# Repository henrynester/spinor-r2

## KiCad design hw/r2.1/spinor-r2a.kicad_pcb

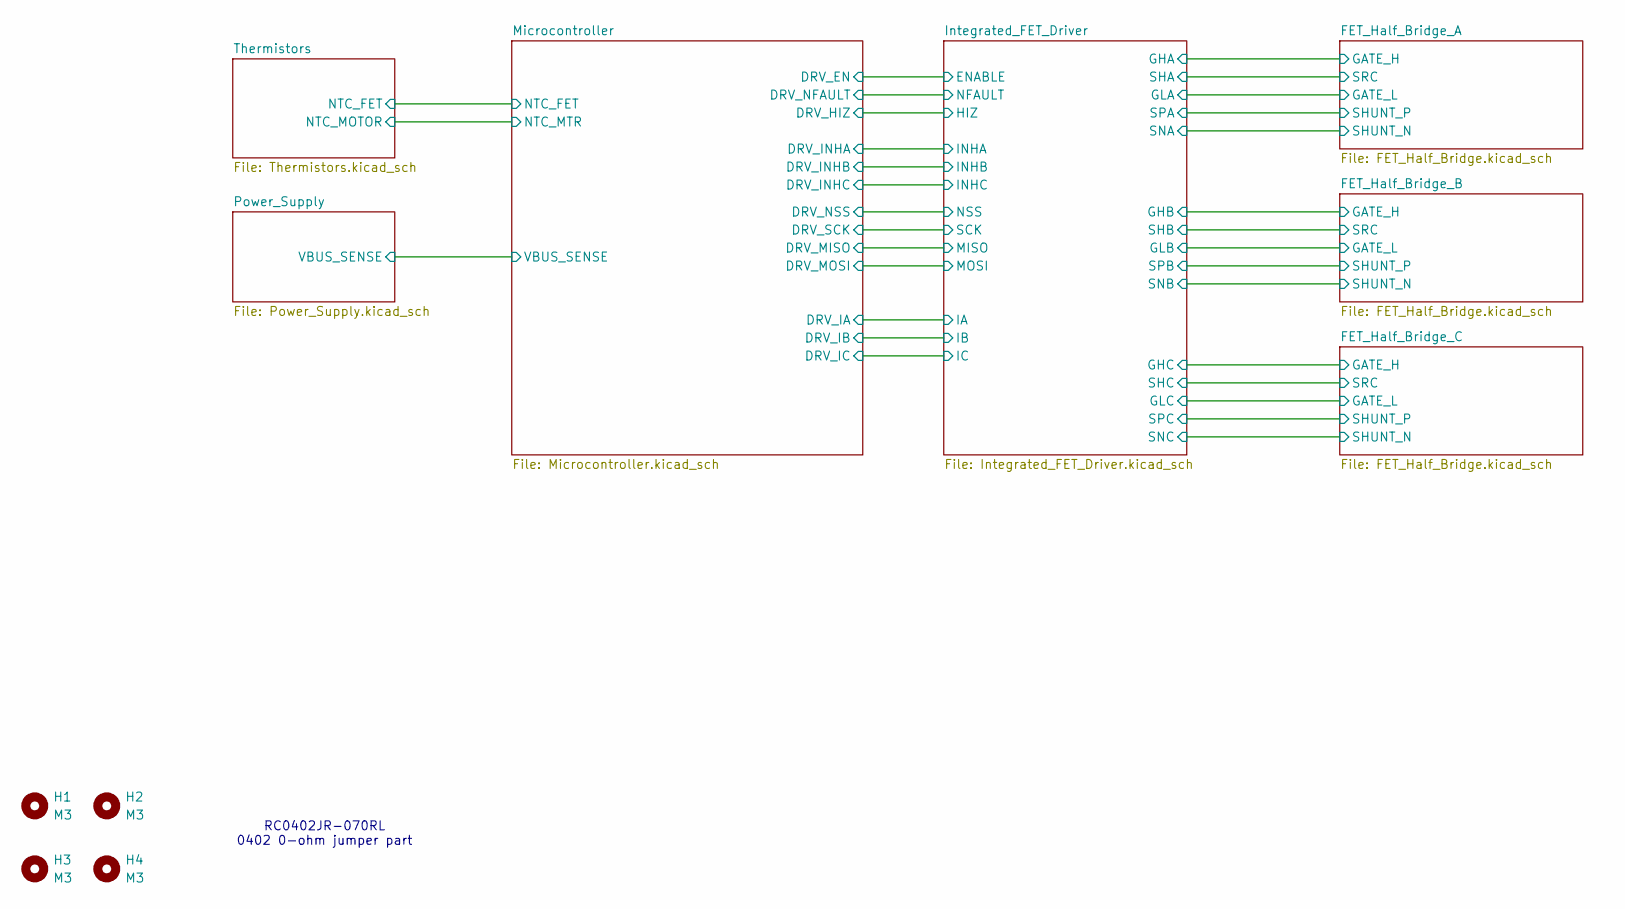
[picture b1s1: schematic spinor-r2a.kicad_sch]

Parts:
H1, H2, H3, H4: M3; MountingHole_3.2mm_M3_Pad_Via

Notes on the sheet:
RC0402JR-070RL 0402 0-ohm jumper part

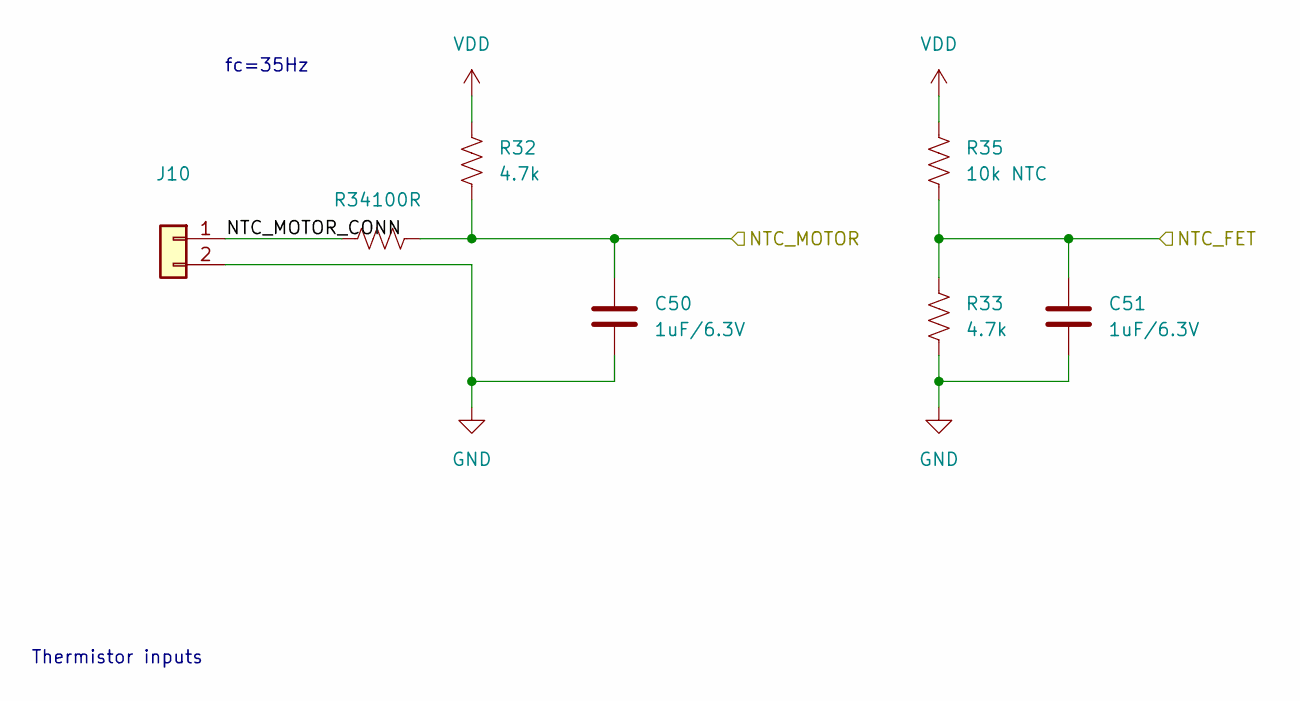
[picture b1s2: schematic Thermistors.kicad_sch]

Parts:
C50, C51: 1uF/6.3V; hn_C_0402; part Murata GRM155R70J105KA12D
J10: PinHeader_1x02_P1.27mm_Vertical
R32, R33: 4.7k; hn_R_0402; part YAGEO RC0402JR-074K7L
R34: 100R; hn_R_0402; part YAGEO RC0402FR-07100RL
R35: 10k NTC; hn_R_0805; part Murata NCP21XV103J03RA

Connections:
/Microcontroller/ADC12_IN1: C50.1, R32.2, R34.2; also elsewhere on the board
/Microcontroller/ADC12_IN2: C51.1, R33.1, R35.2; also elsewhere on the board
/Thermistors/NTC_MOTOR_CONN: J10.1, R34.1
GND: C50.2, C51.2, J10.2, R33.2; also elsewhere on the board

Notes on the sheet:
fc=35Hz
Thermistor inputs

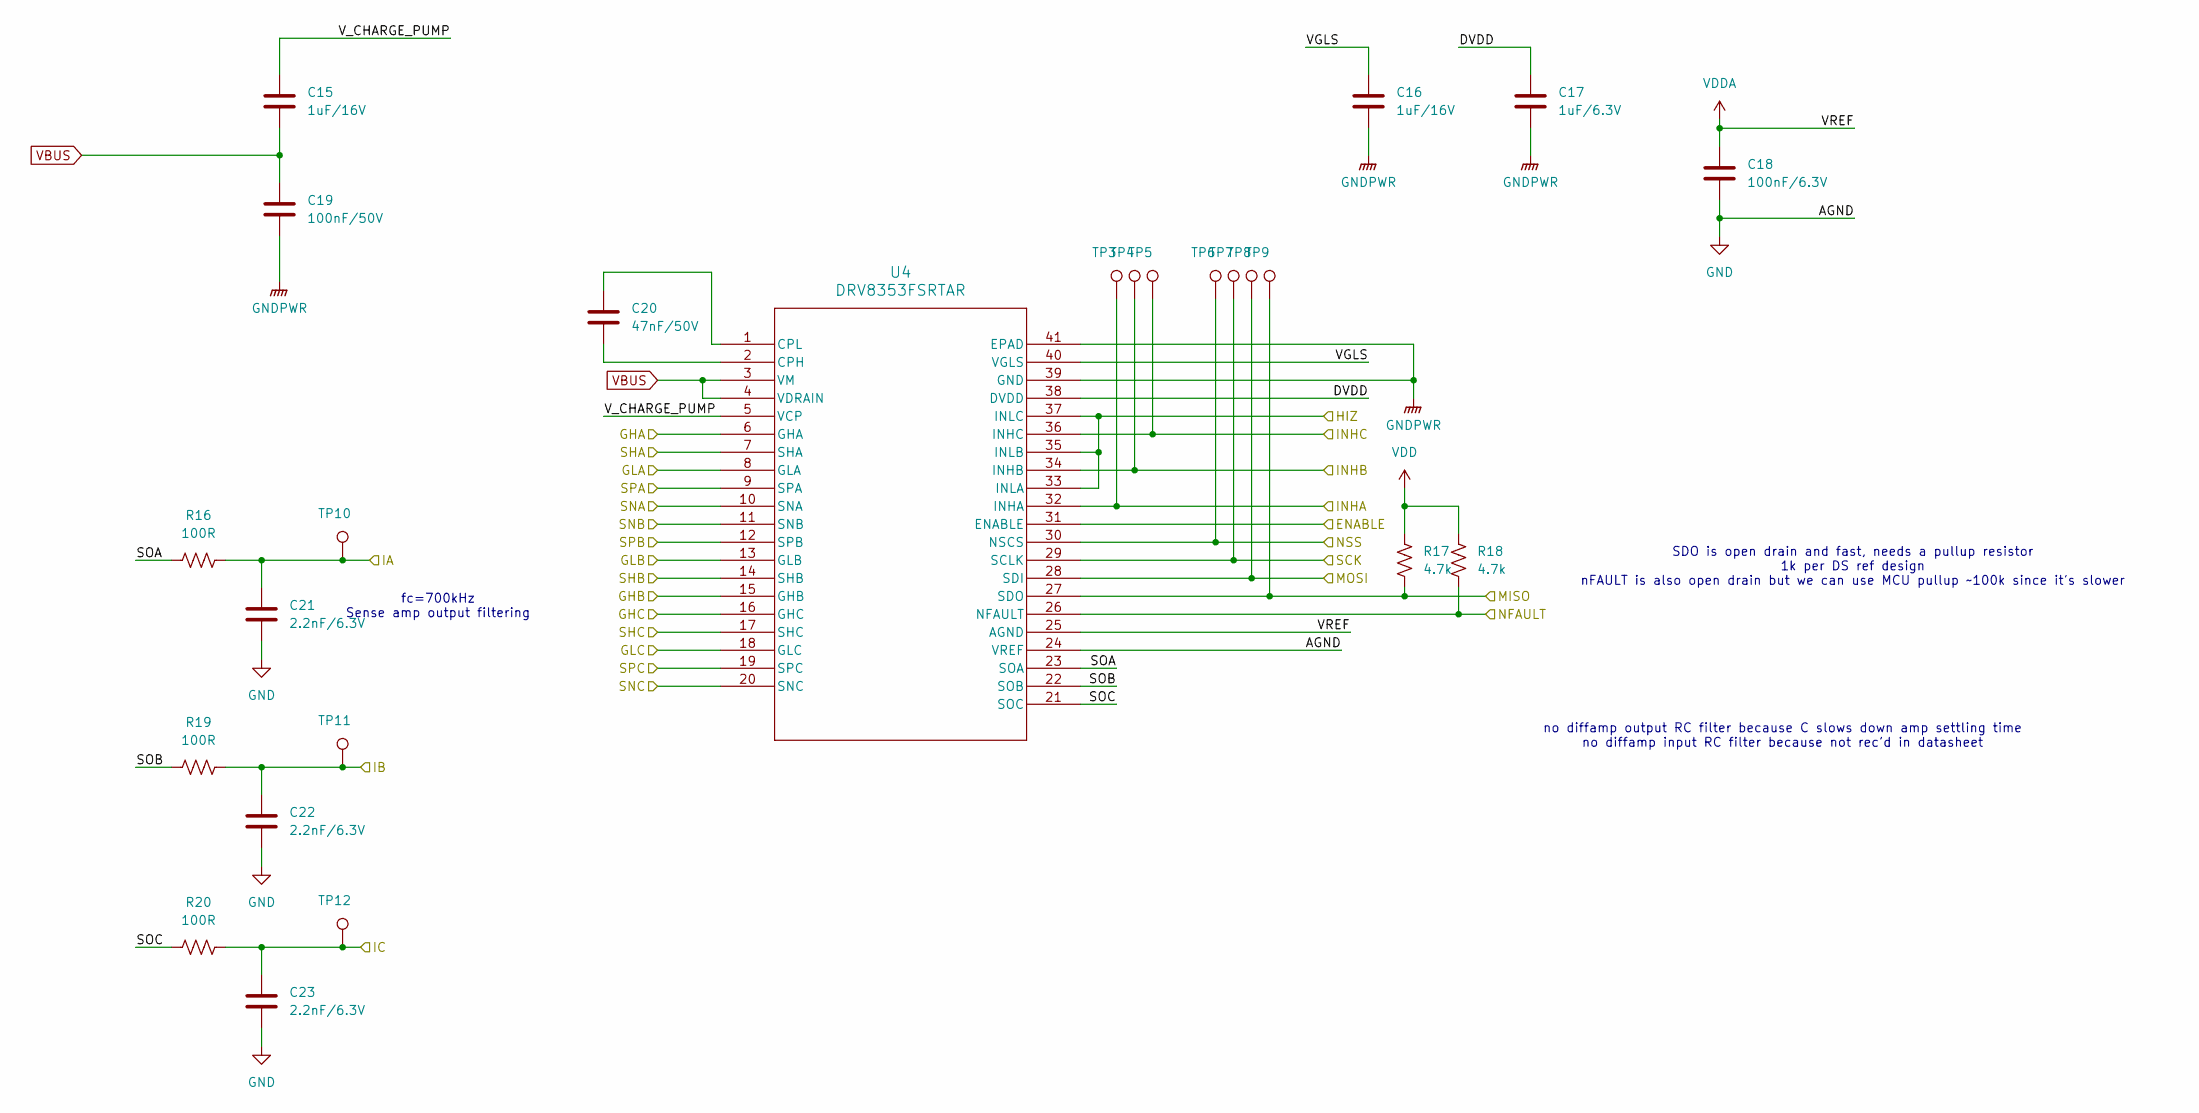
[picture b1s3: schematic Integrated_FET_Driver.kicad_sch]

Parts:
C15, C16: 1uF/16V; hn_C_0603; part Murata GCM188R71C105KA64D
C17: 1uF/6.3V; hn_C_0402; part Murata GRM155R70J105KA12D
C18: 100nF/6.3V; hn_C_0402; part Murata GRM155R70J104KA01D
C19: 100nF/50V; hn_C_0603; part Murata GCJ188R71H104KA12D
C20: 47nF/50V; hn_C_0402; part Murata GRM155R71H473KE14D
C21, C22, C23: 2.2nF/6.3V; hn_C_0402; part Murata GRM155R70J222KA01D
R16, R19, R20: 100R; hn_R_0402; part YAGEO RC0402FR-07100RL
R17, R18: 4.7k; hn_R_0402; part YAGEO RC0402JR-074K7L
TP3, TP4, TP5, TP6, TP7, TP8, TP9, TP10, TP11, TP12: PinHeader_1x01_P1.00mm_Vertical
U4: DRV8353FSRTAR; hn_TexasInstruments_WQFN40; part Texas Instruments DRV8353FSRTAR

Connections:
/FET_Half_Bridge_A/GATE_H: U4.6 (GHA); also elsewhere on the board
/FET_Half_Bridge_A/GATE_L: U4.8 (GLA); also elsewhere on the board
/FET_Half_Bridge_A/PHASE: U4.7 (SHA); also elsewhere on the board
/FET_Half_Bridge_A/SHUNT_P: U4.9 (SPA); also elsewhere on the board
/FET_Half_Bridge_B/GATE_H: U4.15 (GHB); also elsewhere on the board
/FET_Half_Bridge_B/GATE_L: U4.13 (GLB); also elsewhere on the board
/FET_Half_Bridge_B/PHASE: U4.14 (SHB); also elsewhere on the board
/FET_Half_Bridge_B/SHUNT_P: U4.12 (SPB); also elsewhere on the board
/FET_Half_Bridge_C/GATE_H: U4.16 (GHC); also elsewhere on the board
/FET_Half_Bridge_C/GATE_L: U4.18 (GLC); also elsewhere on the board
/FET_Half_Bridge_C/PHASE: U4.17 (SHC); also elsewhere on the board
/FET_Half_Bridge_C/SHUNT_P: U4.19 (SPC); also elsewhere on the board
/Integrated_FET_Driver/DVDD: C17.1, U4.38 (DVDD)
/Integrated_FET_Driver/SOA: R16.1, U4.23 (SOA)
/Integrated_FET_Driver/SOB: R19.1, U4.22 (SOB)
/Integrated_FET_Driver/SOC: R20.1, U4.21 (SOC)
/Integrated_FET_Driver/VGLS: C16.2, U4.40 (VGLS)
/Integrated_FET_Driver/V_CHARGE_PUMP: C15.2, U4.5 (VCP)
/Microcontroller/ADC1_IN12: C21.1, R16.2, TP10.1; also elsewhere on the board
/Microcontroller/ADC2_IN12: C22.1, R19.2, TP11.1; also elsewhere on the board
/Microcontroller/ADC3_IN12: C23.1, R20.2, TP12.1; also elsewhere on the board
/Microcontroller/PA7: U4.31 (ENABLE); also elsewhere on the board
/Microcontroller/PA11: U4.33 (INLA), U4.35 (INLB), U4.37 (INLC); also elsewhere on the board
/Microcontroller/PA12: R18.2, U4.26 (NFAULT); also elsewhere on the board
/Microcontroller/SPI1_MISO: R17.2, TP9.1, U4.27 (SDO); also elsewhere on the board
/Microcontroller/SPI1_MOSI: TP8.1, U4.28 (SDI); also elsewhere on the board
/Microcontroller/SPI1_NSS: TP6.1, U4.30 (NSCS); also elsewhere on the board
/Microcontroller/SPI1_SCK: TP7.1, U4.29 (SCLK); also elsewhere on the board
/Microcontroller/TIM1_CH1: TP3.1, U4.32 (INHA); also elsewhere on the board
/Microcontroller/TIM1_CH2: TP4.1, U4.34 (INHB); also elsewhere on the board
/Microcontroller/TIM1_CH3: TP5.1, U4.36 (INHC); also elsewhere on the board
GND: C16.1, C17.2, C18.2, C19.2, C21.2, C22.2, C23.2, U4.10 (SNA), U4.11 (SNB), U4.20 (SNC), U4.24 (VREF), U4.39 (GND), U4.41 (EPAD); also elsewhere on the board
unnamed: C20.2, U4.2 (CPH)
unnamed: C20.1, U4.1 (CPL)
VBUS: C15.1, C19.1, U4.3 (VM), U4.4 (VDRAIN); also elsewhere on the board

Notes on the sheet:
SDO is open drain and fast, needs a pullup resistor 1k per DS ref design nFAULT is also open drain but we can use MCU pullup ~100k since it's slower
fc=700kHz Sense amp output filtering
no diffamp output RC filter because C slows down amp settling time no diffamp input RC filter because not rec'd in datasheet

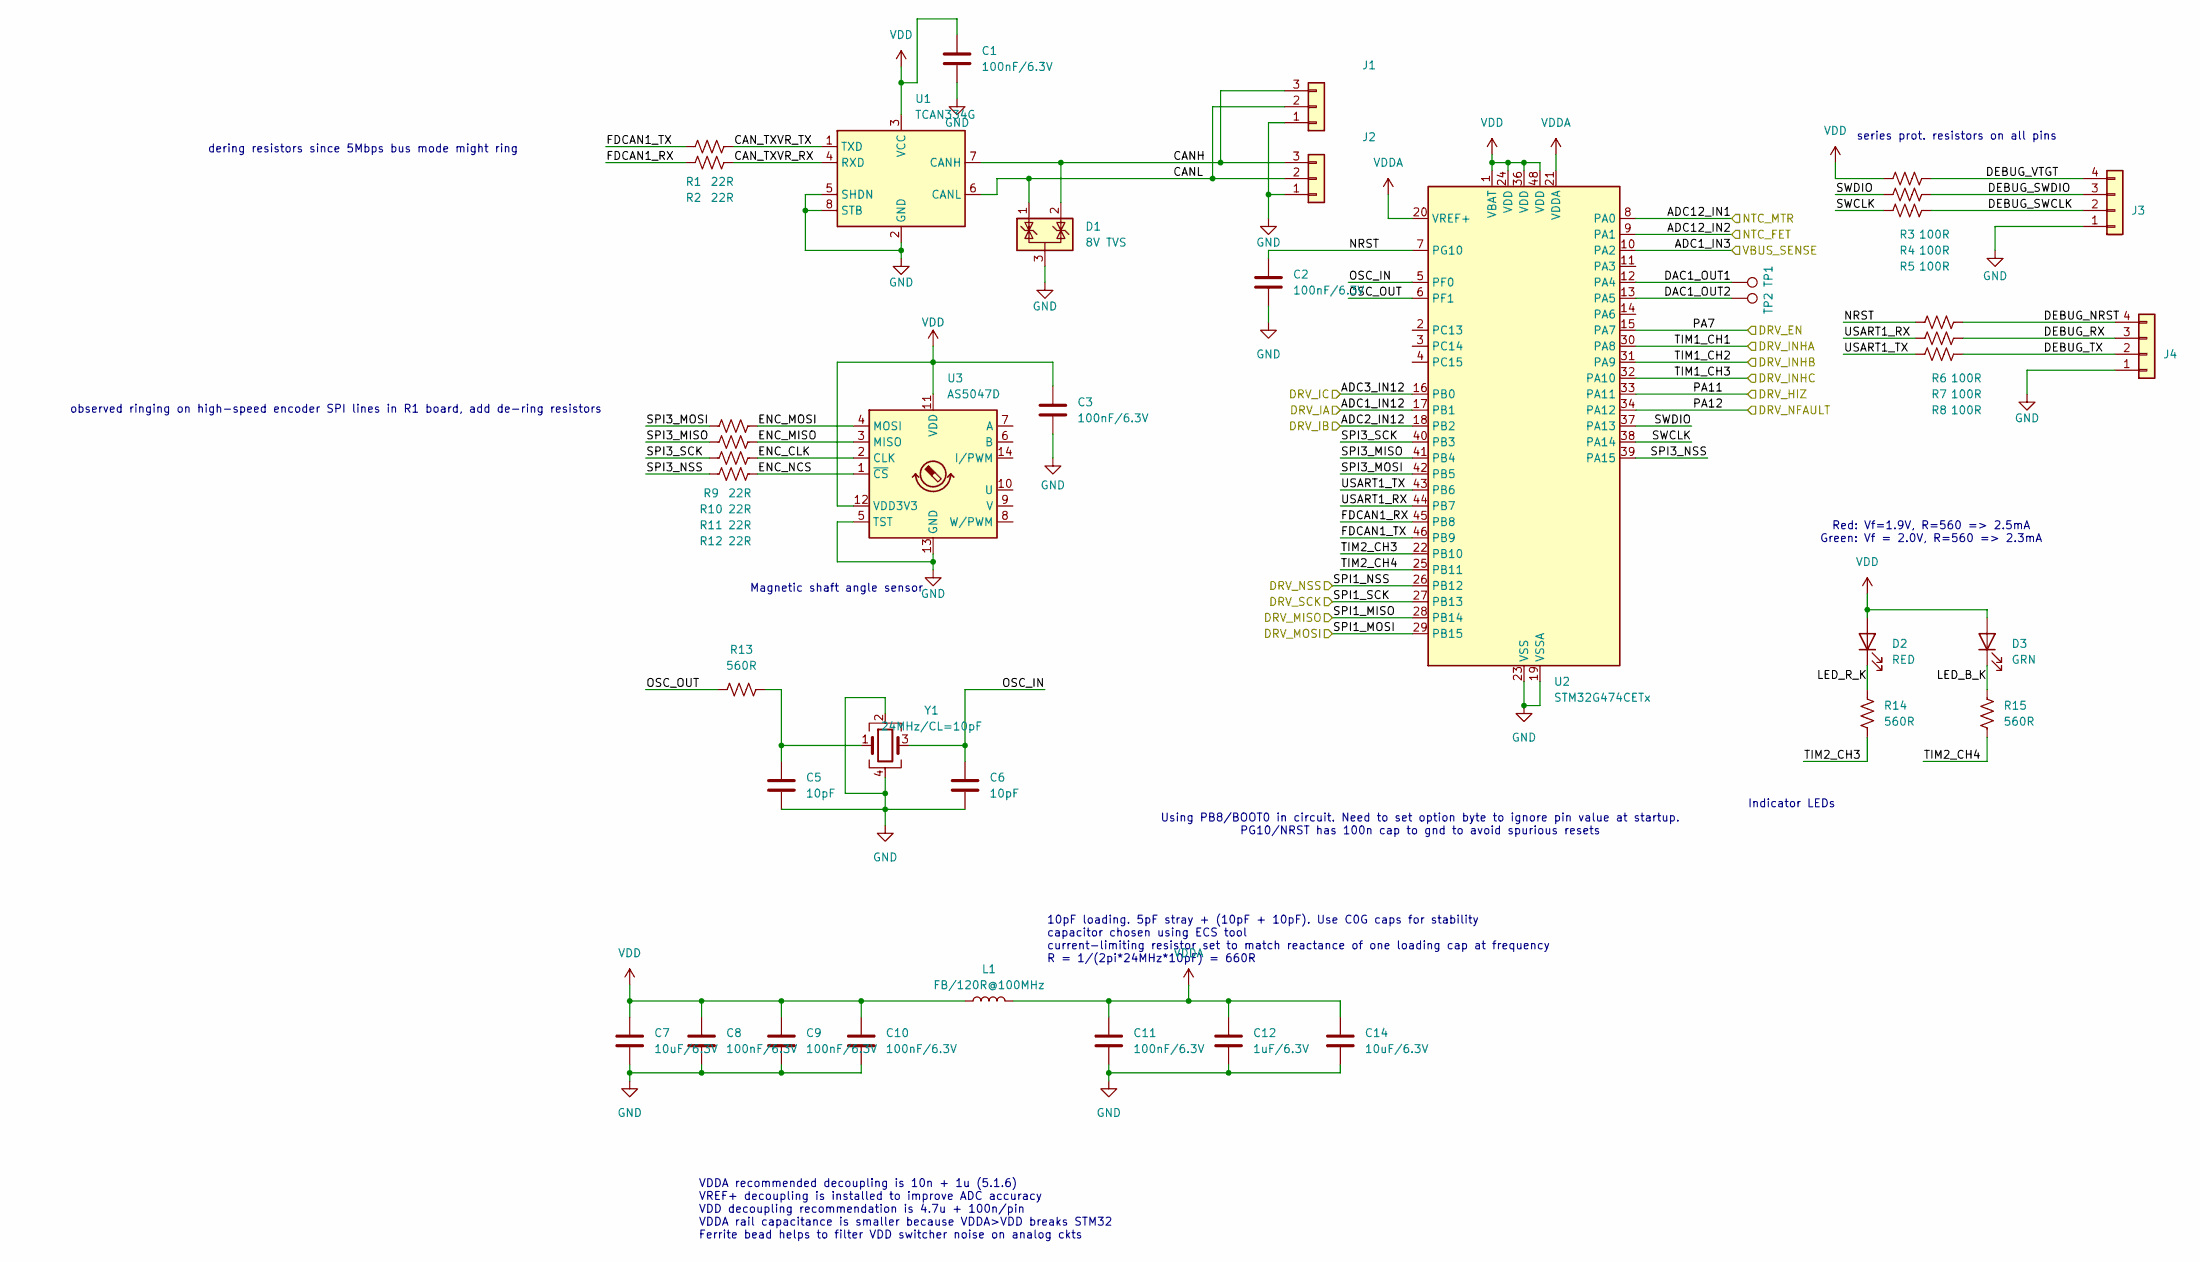
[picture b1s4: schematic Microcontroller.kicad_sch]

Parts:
C1, C2, C3, C8, C9, C10, C11: 100nF/6.3V; hn_C_0402; part Murata GRM155R70J104KA01D
C5, C6: 10pF; hn_C_0402; part Murata GRM1555C1H100FA01D
C7, C14: 10uF/6.3V; hn_C_0805; part Murata GCM21BR70J106KE22L
C12: 1uF/6.3V; hn_C_0402; part Murata GRM155R70J105KA12D
D1: 8V TVS; hn_SOT-23-3; part Wurth 824022
D2: RED; hn_LED_LiteOn; part LiteOn LTST-C171KRKT
D3: GRN; hn_LED_LiteOn; part LiteOn LTST-C171TGKT
J1, J2: hn_JST_XH_S3B-XH-SM4-TB_1x03-1MP_P2.50mm_Horizontal; part JST S3B-XH-SM4-TB
J3, J4: PinHeader_1x04_P1.27mm_Vertical
L1: FB/120R@100MHz; hn_R_0805; part Laird SiLaird HI0805O121R-10
R1, R2, R9, R10, R11, R12: 22R; hn_R_0402; part YAGEO RC0402FR-0722RL
R3, R4, R5, R6, R7, R8: 100R; hn_R_0402; part YAGEO RC0402FR-07100RL
R13, R14, R15: 560R; hn_R_0402; part YAGEO RC0402JR-07560RL
TP1, TP2: PinHeader_1x01_P1.00mm_Vertical
U1: TCAN334G; hn_SOIC8; part Texas Instruments TCAN334G
U2: STM32G474CETx; hn_LQFP48; part STMicroelectronics STM32G474CET6
U3: AS5047D; hn_TSSOP14; part AMS Osram AS5047D
Y1: 24MHz/CL=10pF; hn_XTAL; part ECS ECS-240-10-36-JGN-TR

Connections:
/Microcontroller/ADC1_IN3: U2.10 (PA2); also elsewhere on the board
/Microcontroller/ADC1_IN12: U2.16 (PB0); also elsewhere on the board
/Microcontroller/ADC2_IN12: U2.17 (PB1); also elsewhere on the board
/Microcontroller/ADC3_IN12: U2.18 (PB2); also elsewhere on the board
/Microcontroller/ADC12_IN1: U2.8 (PA0); also elsewhere on the board
/Microcontroller/ADC12_IN2: U2.9 (PA1); also elsewhere on the board
/Microcontroller/CAN_N: D1.1 (K), J1.2, J2.2, U1.6 (CANL)
/Microcontroller/CAN_P: D1.2 (K), J1.3, J2.3, U1.7 (CANH)
/Microcontroller/CAN_TXVR_RX: R2.1, U1.4 (RXD)
/Microcontroller/CAN_TXVR_TX: R1.1, U1.1 (TXD)
/Microcontroller/DAC1_OUT1: TP1.1, U2.12 (PA4)
/Microcontroller/DAC1_OUT2: TP2.1, U2.13 (PA5)
/Microcontroller/DEBUG_NRST: J4.4, R6.2; also elsewhere on the board
/Microcontroller/DEBUG_SWCLK: J3.2, R5.2; also elsewhere on the board
/Microcontroller/DEBUG_SWDIO: J3.3, R4.2; also elsewhere on the board
/Microcontroller/DEBUG_VTGT: J3.4, R3.2; also elsewhere on the board
/Microcontroller/ENC_CLK: R11.1, U3.2 (CLK)
/Microcontroller/ENC_MISO: R10.1, U3.3 (MISO)
/Microcontroller/ENC_MOSI: R9.1, U3.4 (MOSI)
/Microcontroller/ENC_NCS: R12.1, U3.1 (~CS)
/Microcontroller/FDCAN1_RX: R2.2, U2.45 (PB8)
/Microcontroller/FDCAN1_TX: R1.2, U2.46 (PB9)
/Microcontroller/LED_B_K: D3.1 (K), R15.2
/Microcontroller/LED_R_K: D2.1 (K), R14.2
/Microcontroller/NRST: C2.1, R6.1, U2.7 (PG10)
/Microcontroller/OSC_IN: C6.1, U2.5 (PF0), Y1.3
/Microcontroller/OSC_OUT: R13.2, U2.6 (PF1)
/Microcontroller/PA7: U2.15 (PA7); also elsewhere on the board
/Microcontroller/PA11: U2.33 (PA11); also elsewhere on the board
/Microcontroller/PA12: U2.34 (PA12); also elsewhere on the board
/Microcontroller/SPI1_MISO: U2.28 (PB14); also elsewhere on the board
/Microcontroller/SPI1_MOSI: U2.29 (PB15); also elsewhere on the board
/Microcontroller/SPI1_NSS: U2.26 (PB12); also elsewhere on the board
/Microcontroller/SPI1_SCK: U2.27 (PB13); also elsewhere on the board
/Microcontroller/SPI3_MISO: R10.2, U2.41 (PB4)
/Microcontroller/SPI3_MOSI: R9.2, U2.42 (PB5)
/Microcontroller/SPI3_NSS: R12.2, U2.39 (PA15)
/Microcontroller/SPI3_SCK: R11.2, U2.40 (PB3)
/Microcontroller/SWCLK: R5.1, U2.38 (PA14)
/Microcontroller/SWDIO: R4.1, U2.37 (PA13)
/Microcontroller/TIM1_CH1: U2.30 (PA8); also elsewhere on the board
/Microcontroller/TIM1_CH2: U2.31 (PA9); also elsewhere on the board
/Microcontroller/TIM1_CH3: U2.32 (PA10); also elsewhere on the board
/Microcontroller/TIM2_CH3: R14.1, U2.22 (PB10)
/Microcontroller/TIM2_CH4: R15.1, U2.25 (PB11)
/Microcontroller/USART1_TX: R8.1, U2.43 (PB6); also elsewhere on the board
GND: C1.2, C2.2, C3.2, C5.2, C6.2, C7.2, C8.2, C9.2, C10.2, C11.2, C12.2, C14.2, D1.3 (A), J1.1, J2.1, J3.1, J4.1, U1.2 (GND), U1.5 (SHDN), U1.8 (STB), U2.19 (VSSA), U2.23 (VSS), U2.35 (VSS), U2.47 (VSS), U3.5 (TST), U3.13 (GND), Y1.2, Y1.4; also elsewhere on the board
unnamed: C5.1, R13.1, Y1.1
unnamed: J4.2, R8.2
unnamed: J4.3, R7.2
unnamed: R7.1, U2.44 (PB7)
VDDA: C11.1, C12.1, C14.1, L1.2, U2.20 (VREF+), U2.21 (VDDA)

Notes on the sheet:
10pF loading. 5pF stray + (10pF + 10pF). Use C0G caps for stability capacitor chosen using ECS tool current-limiting resistor set to match reactance of one loading cap at frequency R = 1/(2pi*24MHz*10pF) = 660R
VDDA recommended decoupling is 10n + 1u (5.1.6) VREF+ decoupling is installed to improve ADC accuracy VDD decoupling recommendation is 4.7u + 100n/pin VDDA rail capacitance is smaller because VDDA>VDD breaks STM32 Ferrite bead helps to filter VDD switcher noise on analog ckts
Indicator LEDs
Using PB8/BOOT0 in circuit. Need to set option byte to ignore pin value at startup. PG10/NRST has 100n cap to gnd to avoid spurious resets
observed ringing on high-speed encoder SPI lines in R1 board, add de-ring resistors
series prot. resistors on all pins
Magnetic shaft angle sensor
dering resistors since 5Mbps bus mode might ring
Red: Vf=1.9V, R=560 => 2.5mA Green: Vf = 2.0V, R=560 => 2.3mA

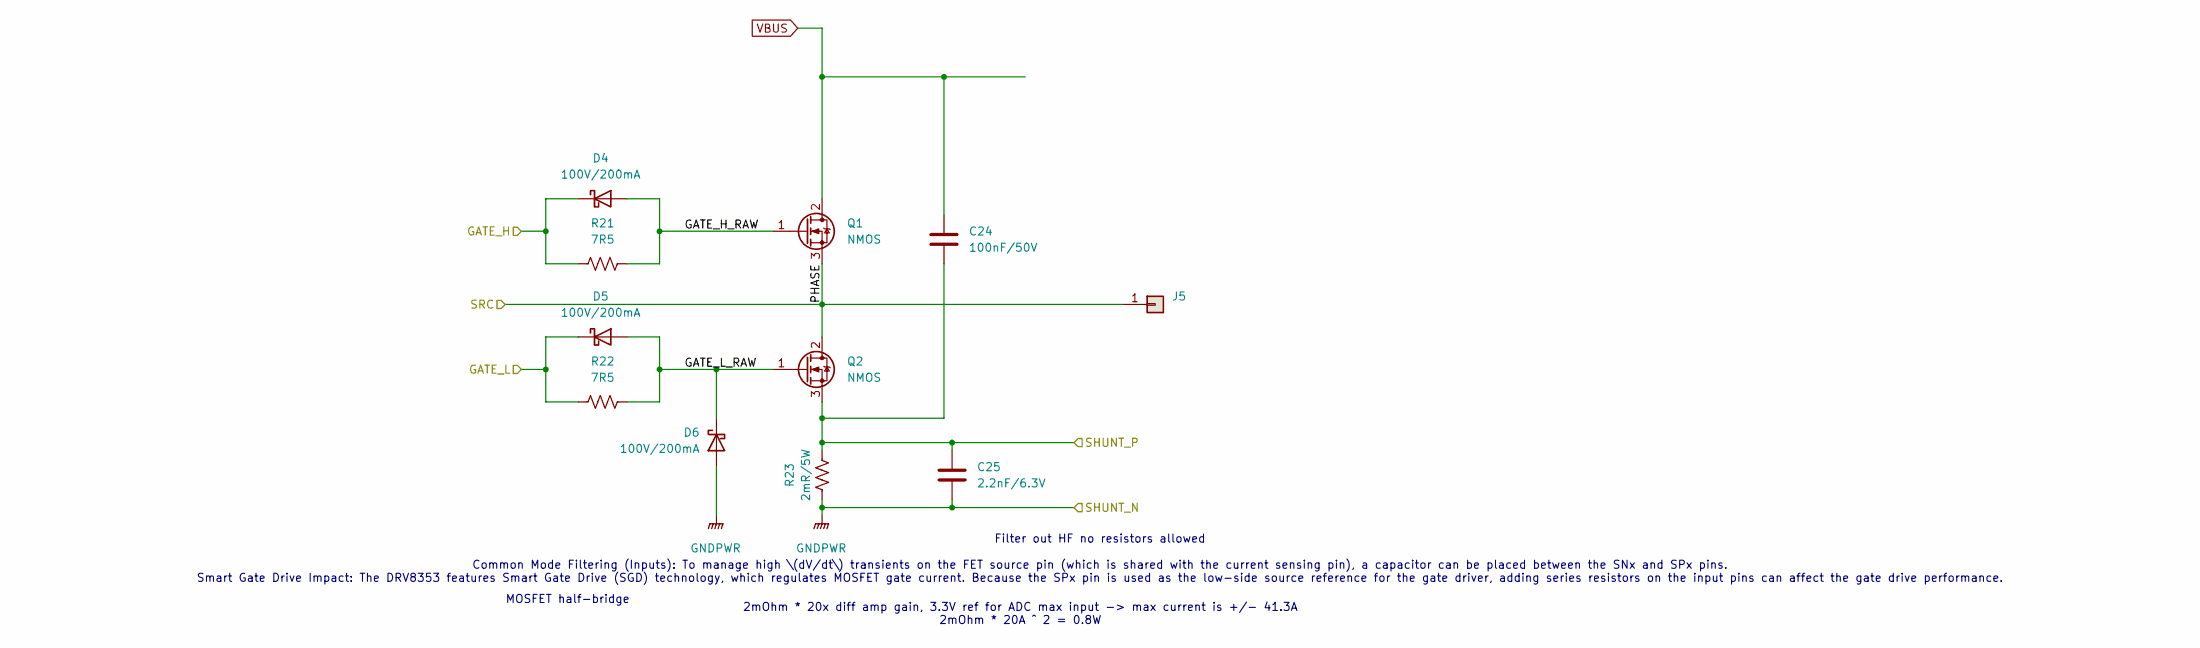
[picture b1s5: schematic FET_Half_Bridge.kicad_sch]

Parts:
C24: 100nF/50V; hn_C_0603; part Murata GCJ188R71H104KA12D
C25: 2.2nF/6.3V; hn_C_0402; part Murata GRM155R70J222KA01D
D4, D5, D6: 100V/200mA; hn_D_SOD-523; part STMicroelectronics BAT41KFILM
J5: SolderWire-1.5sqmm_1x01_D1.7mm_OD3.9mm
Q1, Q2: NMOS; hn_FET_Toshiba_SOPADVANCE8; part Toshiba TPH2R506PL,L1Q
R21, R22: 7R5; hn_R_0402; part YAGEO RC0402FR-077R5L
R23: 2mR/5W; hn_R_2512_shunt; part PEWF2512F2L00Q9

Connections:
/FET_Half_Bridge_A/GATE_H: D4.1 (K), R21.1; also elsewhere on the board
/FET_Half_Bridge_A/GATE_H_RAW: D4.2 (A), Q1.1 (G), R21.2
/FET_Half_Bridge_A/GATE_L: D5.1 (K), R22.1; also elsewhere on the board
/FET_Half_Bridge_A/GATE_L_RAW: D5.2 (A), D6.1 (K), Q2.1 (G), R22.2
/FET_Half_Bridge_A/PHASE: J5.1, Q1.3 (S), Q2.2 (D); also elsewhere on the board
/FET_Half_Bridge_A/SHUNT_P: C24.2, C25.1, Q2.3 (S), R23.1; also elsewhere on the board
GND: C25.2, D6.2 (A), R23.2; also elsewhere on the board
VBUS: C24.1, Q1.2 (D); also elsewhere on the board

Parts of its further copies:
C26, C28: 100nF/50V; hn_C_0603; part Murata GCJ188R71H104KA12D
C27, C29: 2.2nF/6.3V; hn_C_0402; part Murata GRM155R70J222KA01D
D7, D8, D9, D10, D11, D12: 100V/200mA; hn_D_SOD-523; part STMicroelectronics BAT41KFILM
J6, J7: SolderWire-1.5sqmm_1x01_D1.7mm_OD3.9mm
Q3, Q4, Q5, Q6: NMOS; hn_FET_Toshiba_SOPADVANCE8; part Toshiba TPH2R506PL,L1Q
R24, R25, R27, R28: 7R5; hn_R_0402; part YAGEO RC0402FR-077R5L
R26, R29: 2mR/5W; hn_R_2512_shunt; part PEWF2512F2L00Q9

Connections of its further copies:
/FET_Half_Bridge_B/GATE_H: D7.1 (K), R24.1; also elsewhere on the board
/FET_Half_Bridge_B/GATE_H_RAW: D7.2 (A), Q3.1 (G), R24.2
/FET_Half_Bridge_B/GATE_L: D8.1 (K), R25.1; also elsewhere on the board
/FET_Half_Bridge_B/GATE_L_RAW: D8.2 (A), D9.1 (K), Q4.1 (G), R25.2
/FET_Half_Bridge_B/PHASE: J6.1, Q3.3 (S), Q4.2 (D); also elsewhere on the board
/FET_Half_Bridge_B/SHUNT_P: C26.2, C27.1, Q4.3 (S), R26.1; also elsewhere on the board
/FET_Half_Bridge_C/GATE_H: D10.1 (K), R27.1; also elsewhere on the board
/FET_Half_Bridge_C/GATE_H_RAW: D10.2 (A), Q5.1 (G), R27.2
/FET_Half_Bridge_C/GATE_L: D11.1 (K), R28.1; also elsewhere on the board
/FET_Half_Bridge_C/GATE_L_RAW: D11.2 (A), D12.1 (K), Q6.1 (G), R28.2
/FET_Half_Bridge_C/PHASE: J7.1, Q5.3 (S), Q6.2 (D); also elsewhere on the board
/FET_Half_Bridge_C/SHUNT_P: C28.2, C29.1, Q6.3 (S), R29.1; also elsewhere on the board
GND: C27.2, C29.2, D9.2 (A), D12.2 (A), R26.2, R29.2; also elsewhere on the board
VBUS: C26.1, C28.1, Q3.2 (D), Q5.2 (D); also elsewhere on the board

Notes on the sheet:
2mOhm * 20x diff amp gain, 3.3V ref for ADC max input -> max current is +/- 41.3A 2mOhm * 20A ^ 2 = 0.8W
MOSFET half-bridge
Filter out HF no resistors allowed Common Mode Filtering (Inputs): To manage high \(dV/dt\) transients on the FET source pin (which is shared with the current sensing pin), a capacitor can be placed between the SNx and SPx pins. Smart Gate Drive Impact: The DRV8353 features Smart Gate Drive (SGD) t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

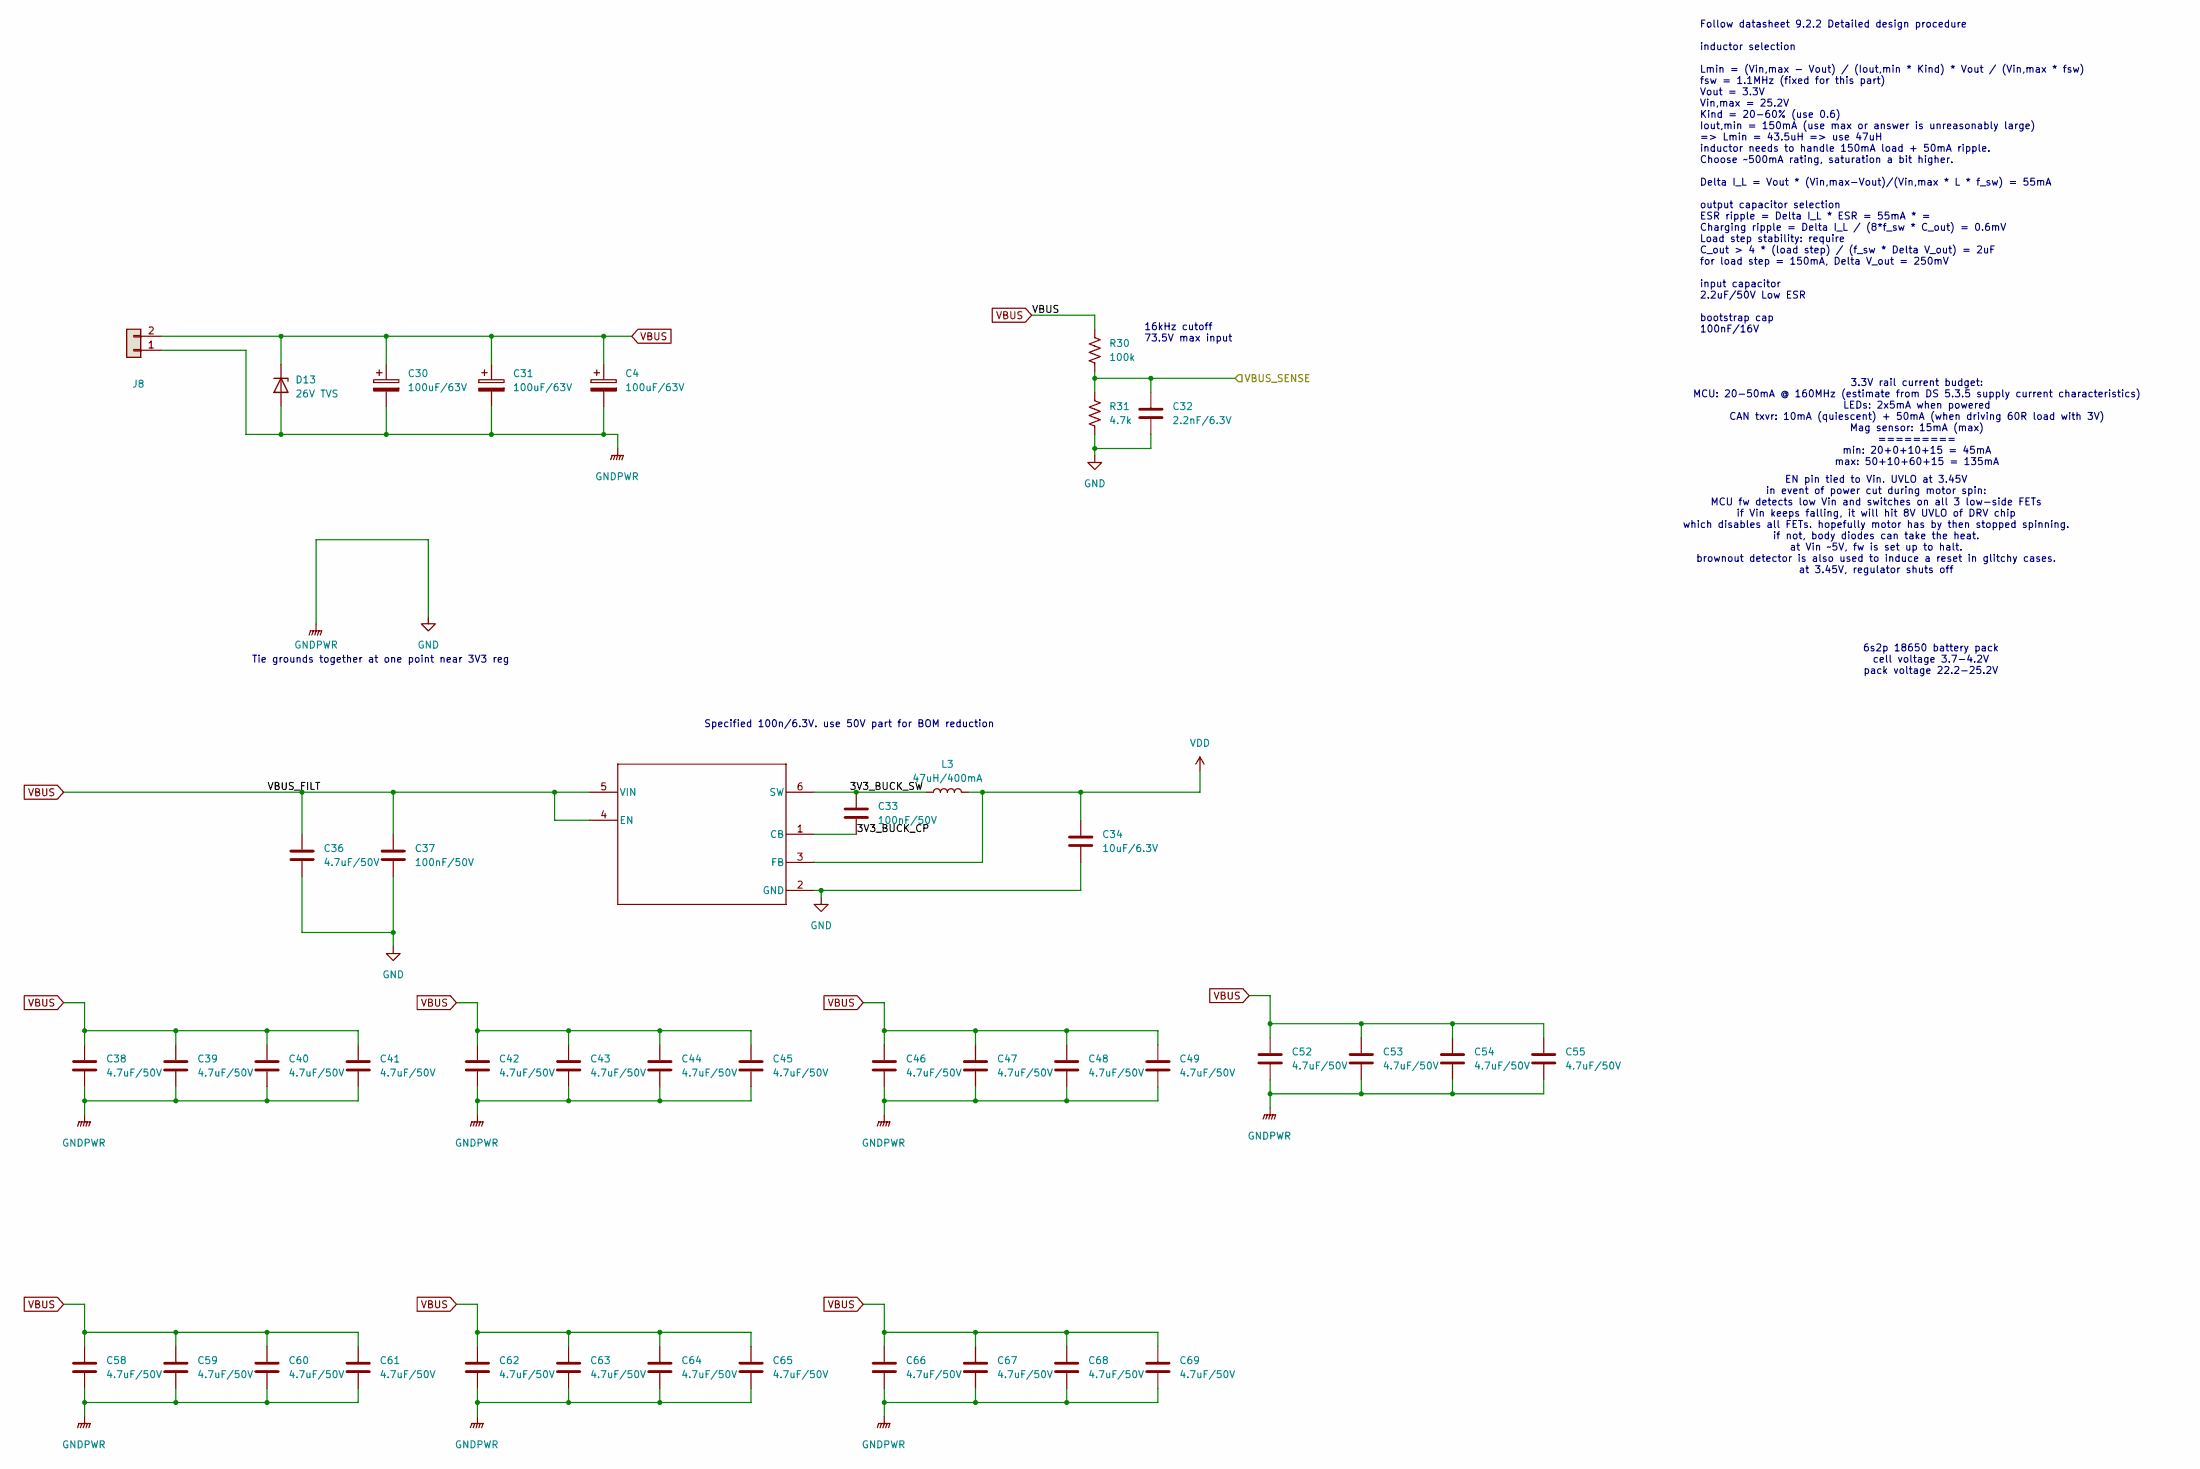
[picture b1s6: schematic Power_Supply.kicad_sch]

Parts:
C4, C30, C31: 100uF/63V; hn_C_Kemet_A768MS; part Kemet A768MS107M1JLAE027
C32: 2.2nF/6.3V; hn_C_0402; part Murata GRM155R70J222KA01D
C33, C37: 100nF/50V; hn_C_0603; part Murata GCJ188R71H104KA12D
C34: 10uF/6.3V; hn_C_0805; part Murata GCM21BR70J106KE22L
C36, C38, C39, C40, C41, C42, C43, C44, C45, C46, C47, C48, C49, C52, C53, C54, C55, C58, C59, C60, C61, C62, C63, C64, C65, C66, C67, C68, C69: 4.7uF/50V; hn_C_1206; part Murata GRM31CR71H475KA12L
D13: 26V TVS; hn_D_SMB; part Littelfuse SMBJ26A
J8: hn_AMASS_XT30PW-M; part Amass XT30-PW-M
L3: 47uH/400mA; hn_L_Bourns_SRN4026; part Bourns SRN4026-470M
R30: 100k; hn_R_0402; part YAGEO RC0402FR-07100KL
R31: 4.7k; hn_R_0402; part YAGEO RC0402JR-074K7L
U5: TPS560430X3FDBVR; hn_TPS560430X3F; part Texas Instruments TPS560430X3FDBVR

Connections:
/Microcontroller/ADC1_IN3: C32.1, R30.2, R31.1; also elsewhere on the board
/Power_Supply/3V3_BUCK_CP: C33.2, U5.1 (CB)
/Power_Supply/3V3_BUCK_SW: C33.1, L3.1, U5.6 (SW)
GND: C4.2, C30.2, C31.2, C32.2, C34.2, C36.2, C37.2, C38.2, C39.2, C40.2, C41.2, C42.2, C43.2, C44.2, C45.2, C46.2, C47.2, C48.2, C49.2, C52.2, C53.2, C54.2, C55.2, C58.2, C59.2, C60.2, C61.2, C62.2, C63.2, C64.2, C65.2, C66.2, C67.2, C68.2, C69.2, D13.2 (A), J8.1, R31.2, U5.2 (GND); also elsewhere on the board
VBUS: C4.1, C30.1, C31.1, C36.1, C37.1, C38.1, C39.1, C40.1, C41.1, C42.1, C43.1, C44.1, C45.1, C46.1, C47.1, C48.1, C49.1, C52.1, C53.1, C54.1, C55.1, C58.1, C59.1, C60.1, C61.1, C62.1, C63.1, C64.1, C65.1, C66.1, C67.1, C68.1, C69.1, D13.1 (K), J8.2, R30.1, U5.4 (EN), U5.5 (VIN); also elsewhere on the board

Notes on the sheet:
Tie grounds together at one point near 3V3 reg
16kHz cutoff 73.5V max input
3.3V rail current budget: MCU: 20-50mA @ 160MHz (estimate from DS 5.3.5 supply current characteristics) LEDs: 2x5mA when powered CAN txvr: 10mA (quiescent) + 50mA (when driving 60R load with 3V) Mag sensor: 15mA (max) ========= min: 20+0+10+15 = 45mA max: 50+10+60+15 = 135mA
Follow datasheet 9.2.2 Detailed design procedure inductor selection Lmin = (Vin,max - Vout) / (Iout,min * Kind) * Vout / (Vin,max * fsw) fsw = 1.1MHz (fixed for this part) Vout = 3.3V Vin,max = 25.2V Kind = 20-60% (use 0.6) Iout,min = 150mA (use max or answer is unreasonably large) => Lmin = 43.5uH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
EN pin tied to Vin. UVLO at 3.45V in event of power cut during motor spin: MCU fw detects low Vin and switches on all 3 low-side FETs if Vin keeps falling, it will hit 8V UVLO of DRV chip which disables all FETs. hopefully motor has by then stopped spinning. if not, body diodes can take the heat. a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
6s2p 18650 battery pack cell voltage 3.7-4.2V pack voltage 22.2-25.2V
Specified 100n/6.3V. use 50V part for BOM reduction

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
